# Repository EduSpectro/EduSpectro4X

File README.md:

# EduSpectro4X
ファームウェア・電子回路
[📖 総合ガイド（Webサイト）はこちら](https://eduspectro.github.io/)

*   **概要**: 「RP2350とC12880MAを組み合わせた分光器の心臓部です」
*   **分光性能諸元**:
    *   測定波長範囲: 340 nm 〜 850 nm（紫外線〜可視光〜近赤外線）
    *   物理画素数: 288 画素（センサー本来の受光素子数）
    *   論理出力点数: 1149 点（4倍オーバーサンプリング間）
    *   波長分解能 (FWHM): 約 10 nm 〜 15 nm
    *   階調分解能: 16bit相当（12bit ADC × 10回累積処理）
    *   最短露光時間: 20 ms（0.02秒）
    *   データ更新間隔: 約 20 ms 〜（露光設定に依存）
*   **特徴**: PIOによる高速制御、10回累積計測してによるノイズ軽減、Catmull-Rom補間など。
*   **必要な環境**:
    *   Arduino IDEのバージョン1.8.19
    *   導入が必要なボードマネージャー（Raspberry Pi Pico/RP2350）
    *   ボード：Waveshare RP2350 Zero、
*   **ハードウェアについて**:
 <dr>

    *   部品リスト：マイコンボード Waveshare RP2350 Zero、分光センサー C12880MA、オペアンプ NJM2732D、0.3mA定電流素子、セラミックコンデンサ 0.1μF(3個)、1kΩ、2kΩ、トグルスイッチ、14ピンICソケット（丸ピン）、ロープロファイルピンヘッダー（オス）、ヘッダーピン(メス)、L型ピンヘッダ（オス）

*   **分光センサー底面と丸ピンICソケットの接触について**:
    *   分光センサーと丸ピンICソケットの間に絶縁シートを挟む。
 <dr>
 <dr>
 <dr>

*   **分光センサーのシリアル番号と波長校正データについて**:
    *   ファームウェアでは波長校正は行なっていません。測定・解析アプリケーションEduSpectroLabの"system_config_do_not_delete"フォルダーの"calibration_coefficients.txt"に使っているセンサーのシリアル番号とデータを書き込む必要があります。

 <dr>
 <dr>

*   [KiCadの使い方について](docs/HowToMakePCB_KiCad×GeminiAI.pdf)<br>
*   **使い方**:
*   [Arduino IDEでの書き込み方](docs/ArduinoIDE_Write_Firm.pdf)
*   Raspberry Pi Pico2などのWebでの記事も参照してください。

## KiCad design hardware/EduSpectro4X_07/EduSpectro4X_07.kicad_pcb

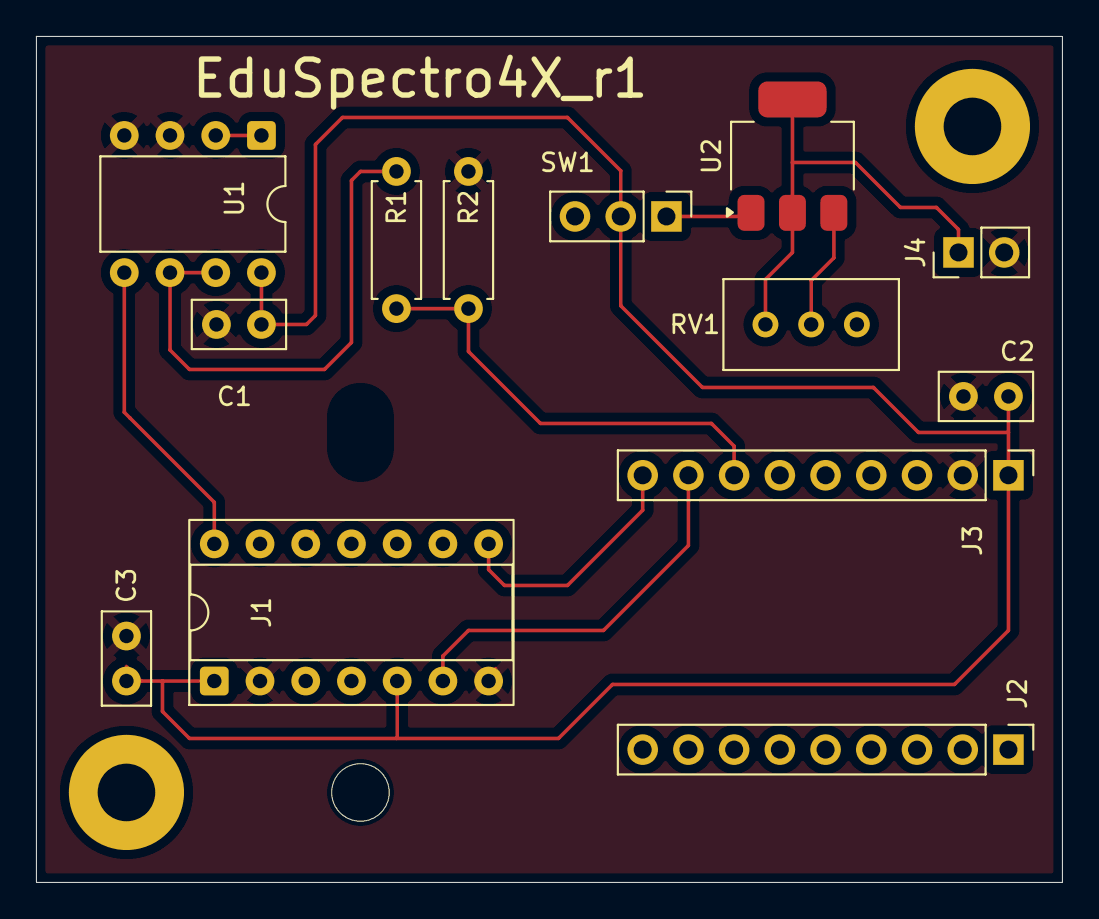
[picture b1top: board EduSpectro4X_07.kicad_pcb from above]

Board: 2 copper layers, 57.0 x 47.0 mm, 13 parts (0 on the bottom side), 11 nets.

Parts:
C1, C2, C3: 0.1u; C_Disc_D5.0mm_W2.5mm_P2.50mm
J1: Conn_02x07_Counter_Clockwise; DIP-14_W7.62mm_Socket
J2, J3: RP2350-Zero; PinHeader_1x09_P2.54mm_Vertical
J4: Conn_01x02_Pin; PinHeader_1x02_P2.54mm_Vertical
R1: 1k; R_Axial_DIN0207_L6.3mm_D2.5mm_P7.62mm_Horizontal
R2: 2k; R_Axial_DIN0207_L6.3mm_D2.5mm_P7.62mm_Horizontal
RV1: 500; Potentiometer_Bourns_3296W_Vertical
SW1: SW_SPDT; PinHeader_1x03_P2.54mm_Vertical
U1: NJM2732; DIP-8_W7.62mm
U2: NSI45020JZ-D; SOT-223-3_TabPin2

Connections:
GND: C1.2, C2.2, C3.2, J1.2, J1.7, J3.2 (GND), J4.2, R2.2, U1.3 (+), U1.4 (V-)
unnamed: C1.1, C2.1, C3.1, J1.1, J1.5, J3.1 (5V), SW1.2 (B), U1.8 (V+)
unnamed: J1.6, J3.8 (GP15)
unnamed: J1.8, J3.9 (GP14)
unnamed: J1.14, U1.5 (+)
unnamed: J3.7 (GP26), R1.2, R2.1
unnamed: J4.1, RV1.3, U2.2 (Cathode)
unnamed: SW1.1 (A), U2.1 (Anode)
unnamed: U1.1, U1.2 (-)
unnamed: R1.1, U1.6 (-), U1.7
unnamed: RV1.2, U2.3 (Radj)

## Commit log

2026-04-26 Create LICENSE
